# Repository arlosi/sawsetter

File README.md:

### Software and KiCad for Handsaw Setting Robot

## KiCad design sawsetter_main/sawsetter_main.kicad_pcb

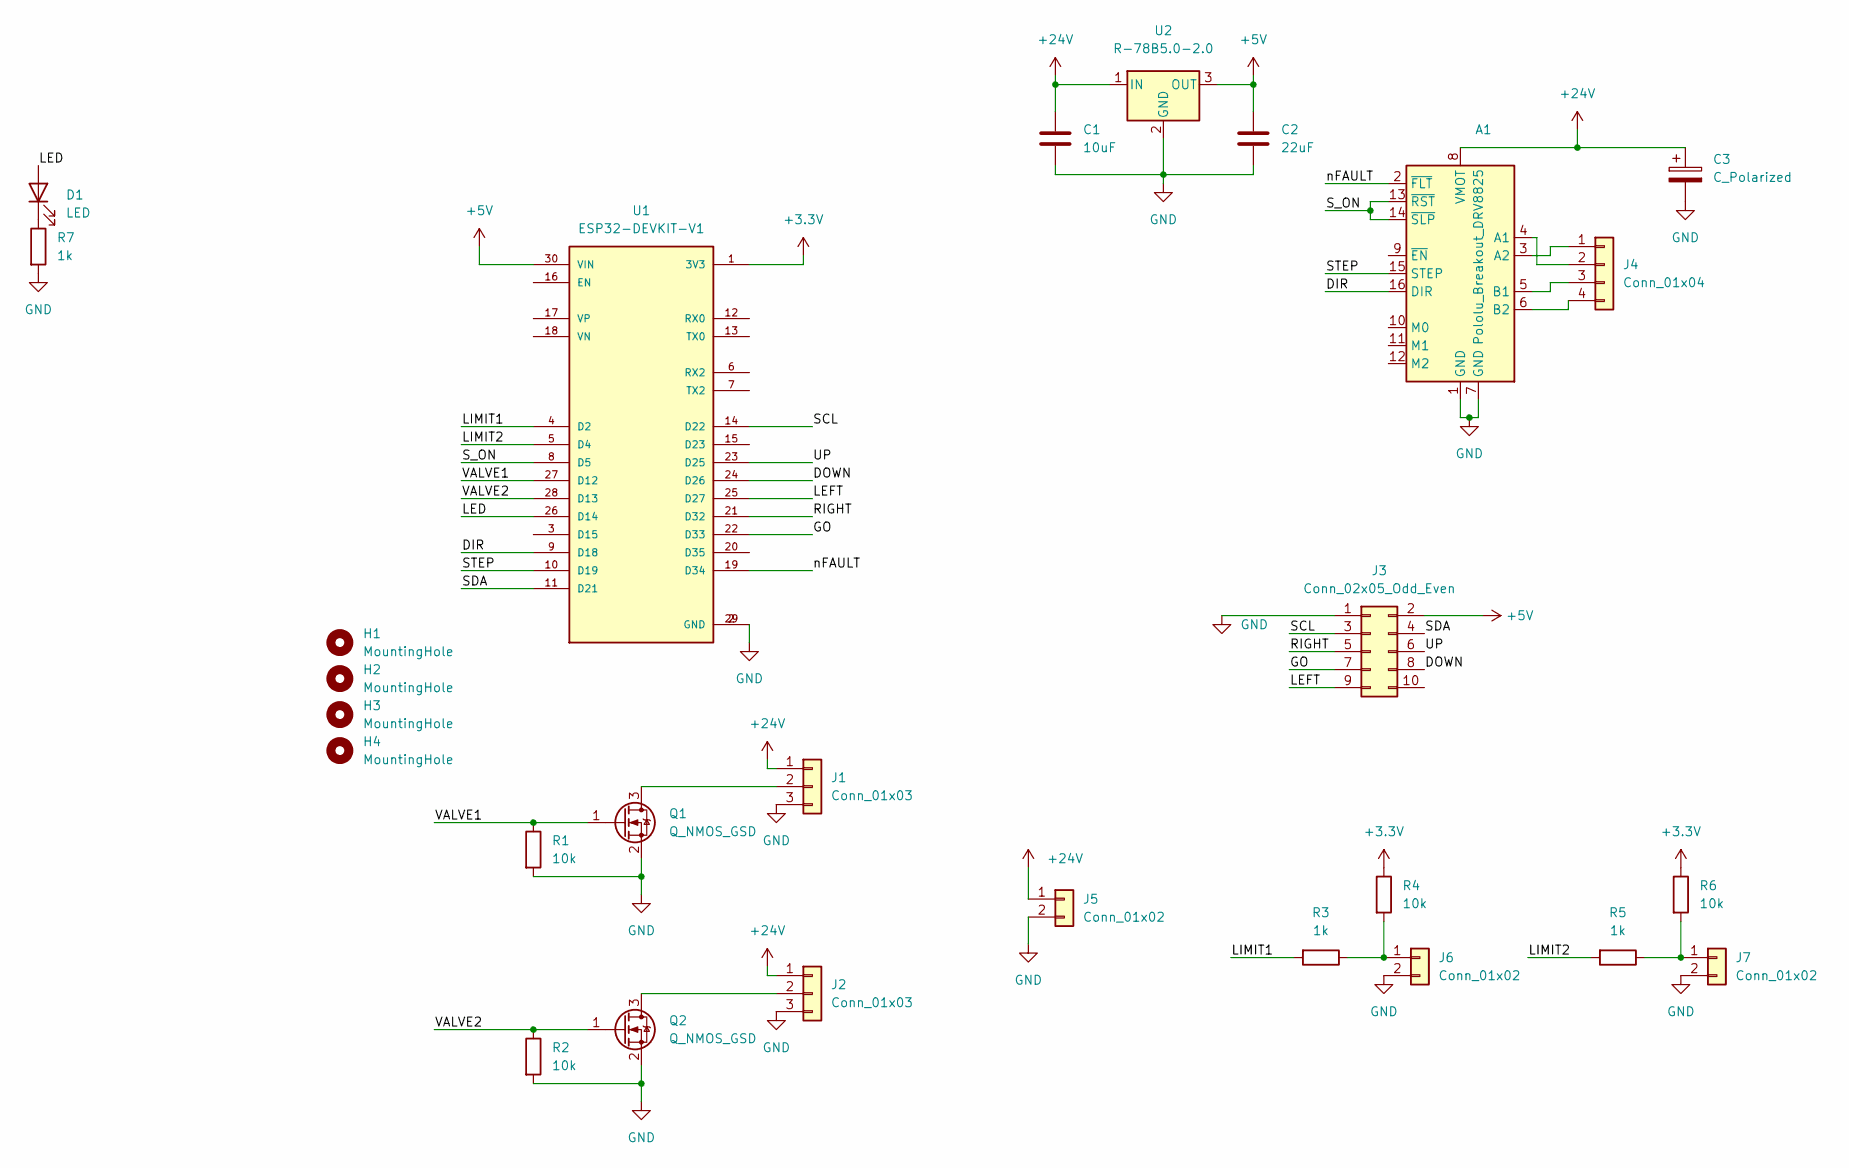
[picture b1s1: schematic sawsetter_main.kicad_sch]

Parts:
A1: Pololu_Breakout_DRV8825; Pololu_Breakout-16_15.2x20.3mm
C1: 10uF; C_1206_3216Metric_Pad1.33x1.80mm_HandSolder
C2: 22uF; C_0603_1608Metric_Pad1.08x0.95mm_HandSolder
C3: C_Polarized; CP_Radial_D10.0mm_P5.00mm
D1: LED; LED_0805_2012Metric_Pad1.15x1.40mm_HandSolder
H1, H2, H3, H4: MountingHole; MountingHole_4.3mm_M4
J1, J2: Conn_01x03; PhoenixContact_MC_1,5_3-G-3.81_1x03_P3.81mm_Horizontal
J3: Conn_02x05_Odd_Even; IDC-Header_2x05_P2.54mm_Vertical
J4: Conn_01x04; PhoenixContact_MC_1,5_4-G-3.81_1x04_P3.81mm_Horizontal
J5: Conn_01x02; PhoenixContact_MC_1,5_2-G-5.08_1x02_P5.08mm_Horizontal
J6, J7: Conn_01x02; PhoenixContact_MC_1,5_2-G-3.81_1x02_P3.81mm_Horizontal
Q1, Q2: Q_NMOS_GSD; TSOT-23_HandSoldering
R1, R2, R4, R6: 10k; R_0603_1608Metric_Pad0.98x0.95mm_HandSolder
R3, R5, R7: 1k; R_0603_1608Metric_Pad0.98x0.95mm_HandSolder
U1: ESP32-DEVKIT-V1; MODULE_ESP32_DEVKIT_V1; PARTREV N/A
U2: R-78B5.0-2.0; Converter_DCDC_RECOM_R-78B-2.0_THT

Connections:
+3V3: R4.1, R6.1, U1.1 (3V3)
+5V: C2.1, J3.2, U1.30 (VIN), U2.3 (OUT)
+24V: A1.8 (VMOT), C1.1, C3.1, J1.1, J2.1, J5.1, U2.1 (IN)
/DIR: A1.16 (DIR), U1.9 (D18)
/DOWN: J3.8, U1.24 (D26)
/GO: J3.7, U1.22 (D33)
/LED: D1.2 (A), U1.26 (D14)
/LEFT: J3.9, U1.25 (D27)
/LIMIT1: R3.2, U1.4 (D2)
/LIMIT2: R5.2, U1.5 (D4)
/RIGHT: J3.5, U1.21 (D32)
/SCL: J3.3, U1.14 (D22)
/SDA: J3.4, U1.11 (D21)
/STEP: A1.15 (STEP), U1.10 (D19)
/S_ON: A1.13 (~RST), A1.14 (~SLP), U1.8 (D5)
/UP: J3.6, U1.23 (D25)
/VALVE1: Q1.1 (G), R1.1, U1.27 (D12)
/VALVE2: Q2.1 (G), R2.1, U1.28 (D13)
/nFAULT: A1.2 (~FLT), U1.19 (D34)
GND: A1.1 (GND), A1.7 (GND), C1.2, C2.2, C3.2, J1.3, J2.3, J3.1, J5.2, J6.2, J7.2, Q1.2 (S), Q2.2 (S), R1.2, R2.2, R7.2, U1.2 (GND), U1.29 (GND), U2.2 (GND)
unnamed: A1.3 (A2), J4.1
unnamed: A1.4 (A1), J4.2
unnamed: A1.5 (B1), J4.3
unnamed: A1.6 (B2), J4.4
unnamed: D1.1 (K), R7.1
unnamed: J1.2, Q1.3 (D)
unnamed: J2.2, Q2.3 (D)
unnamed: J6.1, R3.1, R4.2
unnamed: J7.1, R5.1, R6.2

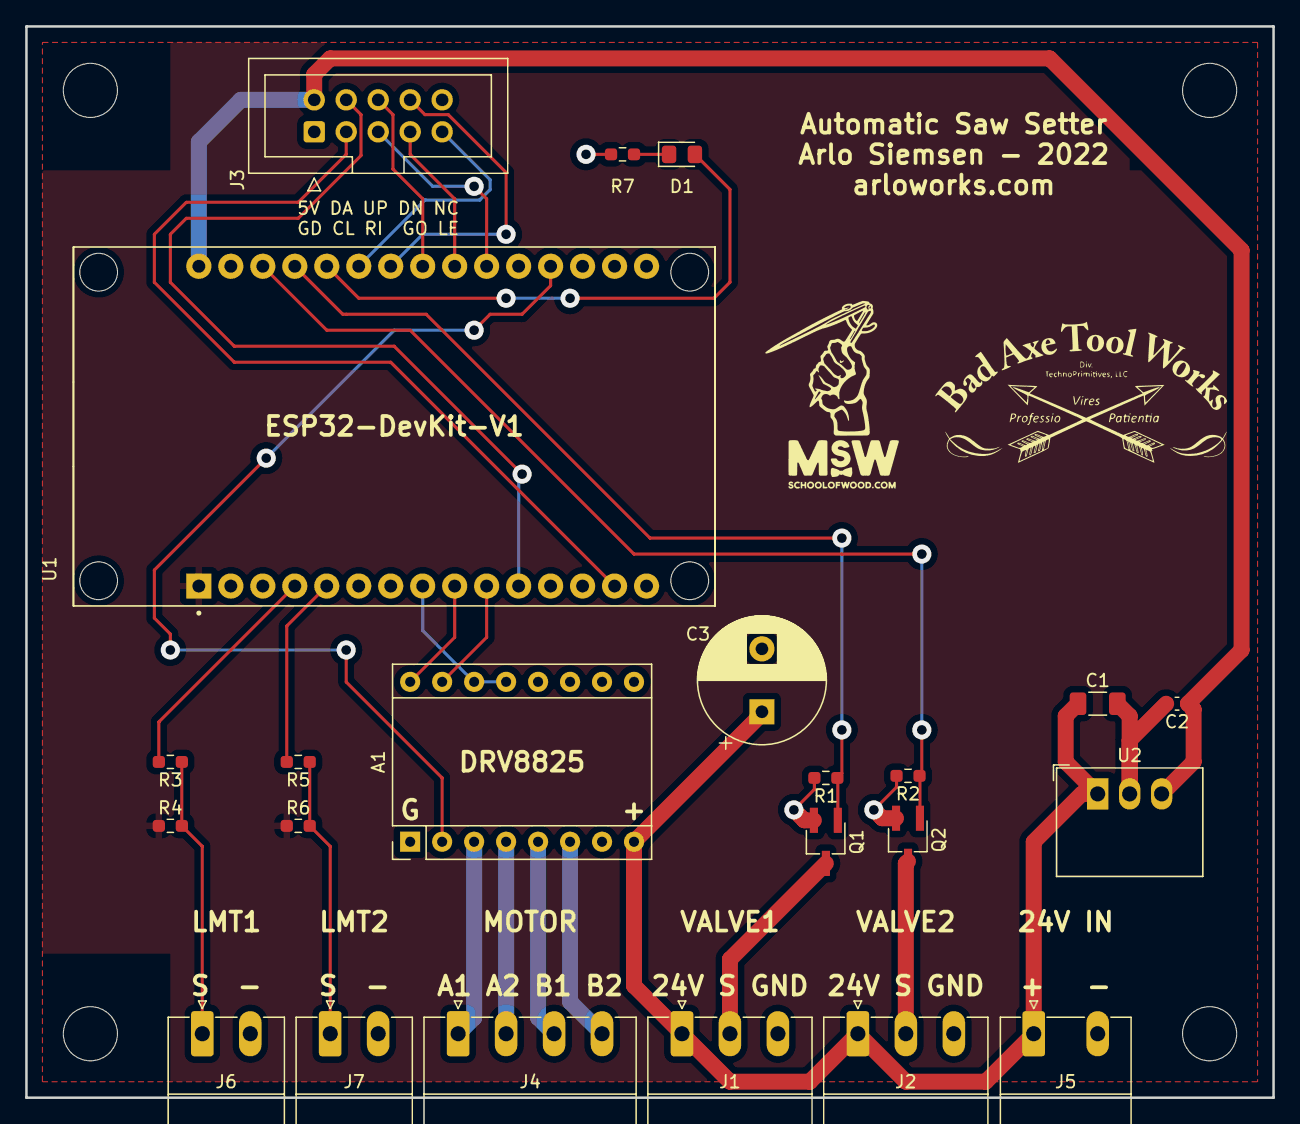
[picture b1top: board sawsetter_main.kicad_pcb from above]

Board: 2 copper layers, 99.1 x 85.1 mm, 27 parts (0 on the bottom side), 29 nets.

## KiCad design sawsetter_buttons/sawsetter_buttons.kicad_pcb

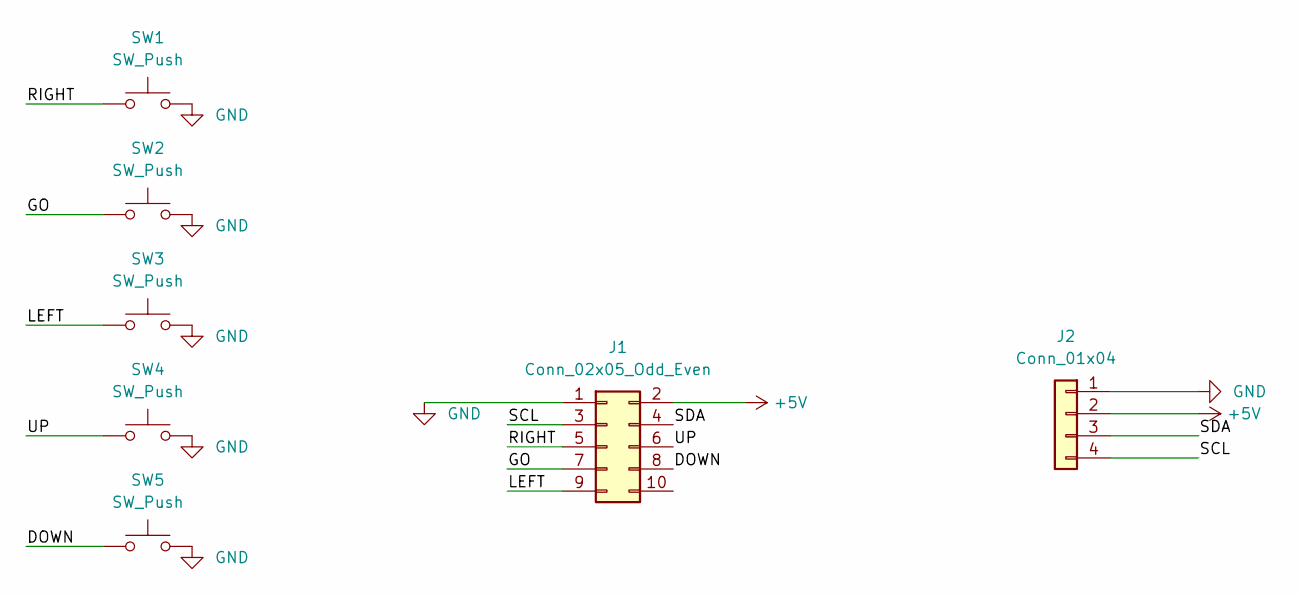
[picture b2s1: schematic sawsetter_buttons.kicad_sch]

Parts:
J1: Conn_02x05_Odd_Even; IDC-Header_2x05_P2.54mm_Vertical
J2: Conn_01x04; PinHeader_1x04_P2.54mm_Horizontal
SW1, SW2, SW3, SW4, SW5: SW_Push; SW_PUSH-12mm_Wuerth-430476085716

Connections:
+5V: J1.2, J2.2
/DOWN: J1.8, SW5.1
/GO: J1.7, SW2.1
/LEFT: J1.9, SW3.1
/RIGHT: J1.5, SW1.1
/SCL: J1.3, J2.4
/SDA: J1.4, J2.3
/UP: J1.6, SW4.1
GND: J1.1, J2.1, SW1.2, SW2.2, SW3.2, SW4.2, SW5.2

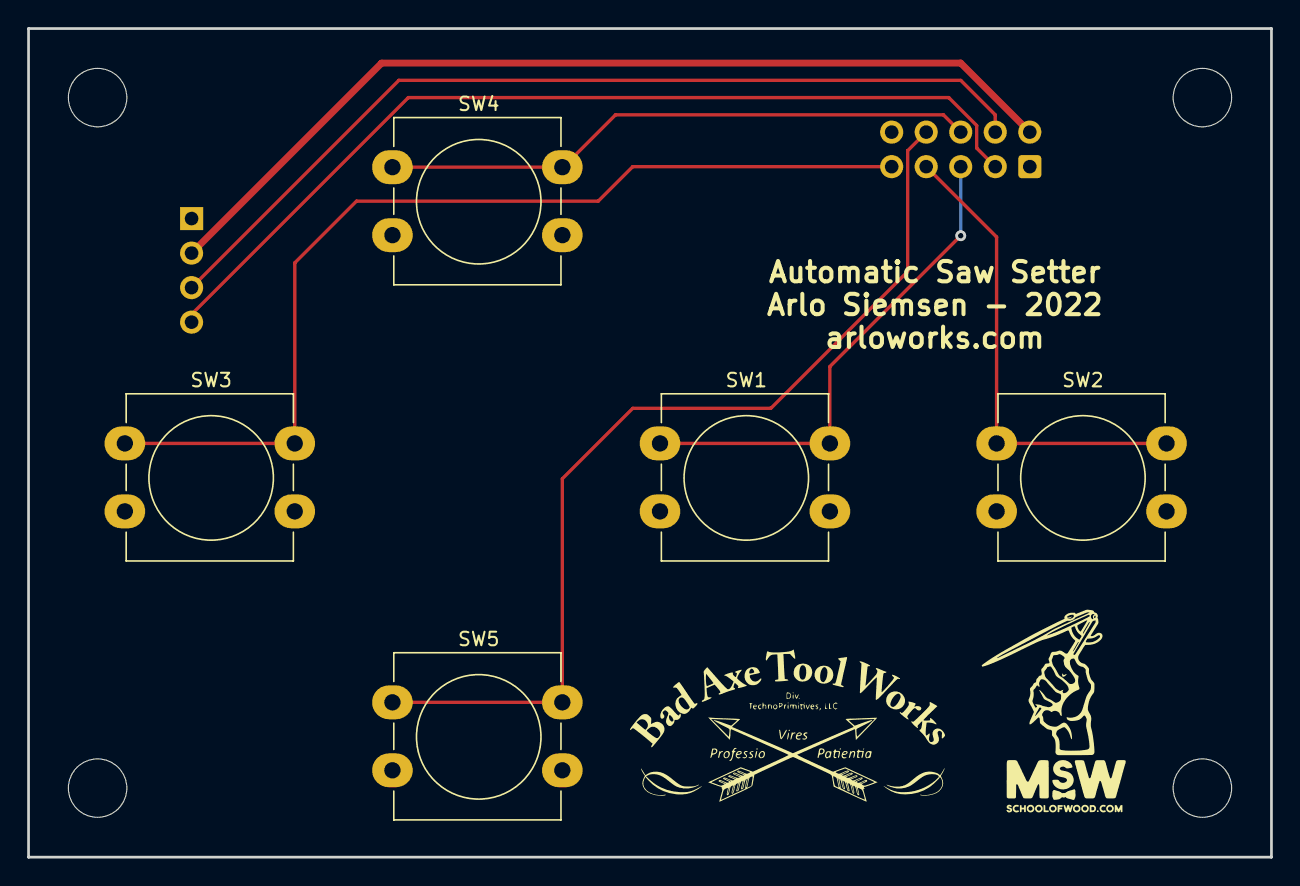
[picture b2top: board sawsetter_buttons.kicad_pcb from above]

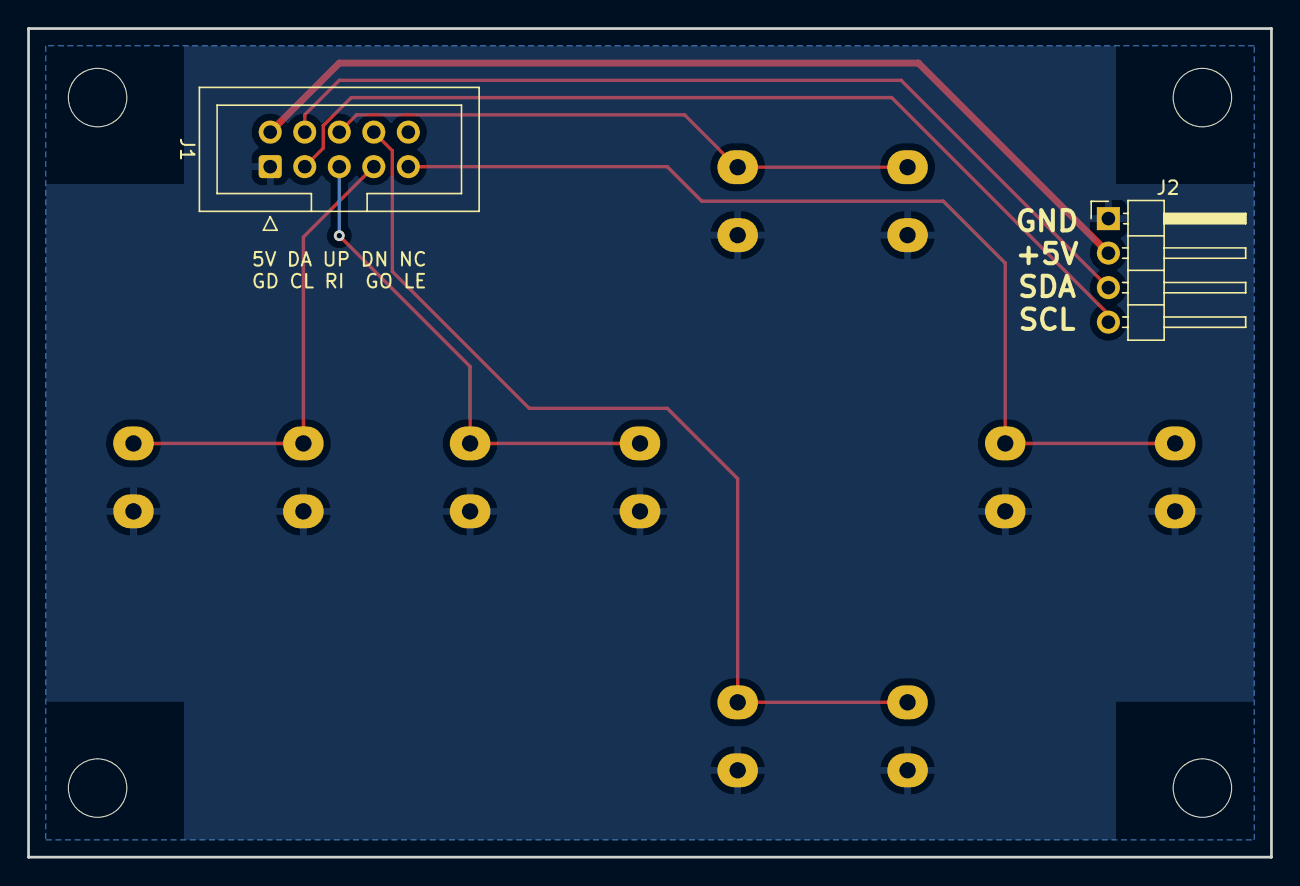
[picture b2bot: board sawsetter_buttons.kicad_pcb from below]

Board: 2 copper layers, 91.4 x 61.0 mm, 11 parts (2 on the bottom side), 9 nets.

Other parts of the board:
H1, H1#2, H1#3, H1#4: MountingHole; MountingHole_4.3mm_M4

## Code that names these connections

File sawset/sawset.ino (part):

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
const int PIN_DIR = 18;
const int PIN_STEP = 19;
const int PIN_NFAULT = 34;
const int PIN_MOTOR_ON = 5;

const int PIN_UP = 25;
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const int PIN_RIGHT = 32;
const int PIN_GO = 33;

const int PIN_LIMIT1 = 2;
const int PIN_LIMIT2 = 4;

const int PIN_VALVE1 = 12;
const int PIN_VALVE2 = 13;

// LCD
const int LCD_ADDR = 0x27;
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    return;
  }

  bool limit_pressed = digitalRead(PIN_LIMIT2);
  
  taskENTER_CRITICAL_ISR(&mux);
  if (limit_pressed && !zero_completed) {
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    switch (option) {
      case LCD_TEST:
        buffer.print("<STR FNC> ");
        buffer.print(digitalRead(PIN_LIMIT1));
        buffer.print(digitalRead(PIN_LIMIT2));
        break;
      case LCD_JOG:
        buffer.print(position);
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  }

  // Retract
  digitalWrite(PIN_VALVE2, true);
  vTaskDelay(200 / portTICK_RATE_MS);

  for (int i = 0; i < count && !_cancel; i++) {
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    move_blocking(start + i * spacing);
    
    // Fire
    digitalWrite(PIN_VALVE1, true);
    vTaskDelay(100 / portTICK_RATE_MS);
    digitalWrite(PIN_VALVE1, false);
    vTaskDelay(75 / portTICK_RATE_MS);
  }

  move_blocking(offset_starting_point(cfg));

  // Extend
  digitalWrite(PIN_VALVE2, false);
  mode = MENU;
  vTaskDelete(NULL);
}
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  Cfg cfg = _cfg.read();

  // Retract
  digitalWrite(PIN_VALVE2, true);
  vTaskDelay(200 / portTICK_RATE_MS);
  int pos1 = cfg.inches_to_ticks() * GRIND_START_IN;
  int pos2 = cfg.inches_to_ticks() * (GRIND_START_IN + GRIND_LENGTH_IN);
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  }

  // Fire
  digitalWrite(PIN_VALVE1, true);
  vTaskDelay(100 / portTICK_RATE_MS);
  buffer.println("Press GO to stop");
  buffer.flush();
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    move_blocking(pos1);
  }
  // Unfire
  digitalWrite(PIN_VALVE1, false);
  mode = MENU;
  vTaskDelete(NULL);
}
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          case LCD_TEST:
            switch (button){
              case BUTTON_LEFT:
                digitalWrite(PIN_VALVE1, true);
                vTaskDelay(100 / portTICK_RATE_MS);
                break;
              case BUTTON_RIGHT:
                digitalWrite(PIN_VALVE2, true);                
                vTaskDelay(100 / portTICK_RATE_MS);
                break;
              case BUTTON_NONE:
                digitalWrite(PIN_VALVE1, false);
                digitalWrite(PIN_VALVE2, false);
                move_nonblocking(starting_point(cfg));
                break;
            }
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  
  pinMode(PIN_DIR, OUTPUT);
  pinMode(PIN_STEP, OUTPUT);
  pinMode(PIN_NFAULT, INPUT);
  pinMode(PIN_MOTOR_ON, OUTPUT);

  pinMode(PIN_LED, OUTPUT);
  pinMode(PIN_VALVE1, OUTPUT);
  pinMode(PIN_VALVE2, OUTPUT);

  pinMode(PIN_LIMIT1, INPUT);
  pinMode(PIN_LIMIT2, INPUT);

  pinMode(PIN_UP, INPUT_PULLUP);
  pinMode(PIN_DOWN, INPUT_PULLUP);
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
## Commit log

2022-04-03 initial prototype working
2022-04-06 Add sleep and EEPROM
2022-08-19 Add length option
2022-08-22 adjust sleep time
2022-08-22 only read cfg once
2022-09-03 Add calibration
2022-09-03 added laser support
2022-09-13 Add length calibration
2022-09-15 Create LICENSE
2022-09-21 Adjust grind length
